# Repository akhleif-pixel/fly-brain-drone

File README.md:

# Fly-Brain Drone

A small ESP32-S3 camera quadcopter steered by a simulated fruit fly brain (FlyWire connectome, Shiu et al. 2024 model) running on a laptop.

- **Plan, phases and tasks:** https://claude.ai/artifact/NuM1vron4UPJLkWDwymUnH
- **Parts with photos and links:** https://claude.ai/artifact/14MLLZMBsPiJeyRGL1XqSZ
- **Project context for Claude:** [CLAUDE.md](CLAUDE.md)

## Folders

| Folder | What goes there | Owner |
| --- | --- | --- |
| `brain/` | Brain model setup and the laptop control loop | Person A |
| `drone/` | ESP32-S3 firmware (PlatformIO) | Person B |
| `frame/` | 3D-print files | Person B |
| `docs/` | Parts, wiring, notes | Both |

## Working together

**Ayham** works with Claude. **Ahmed** works in KiCad 10 on the PCB frame.

Ahmed, to get the files:
1. Accept the GitHub invite (email or github.com/notifications).
2. Install [GitHub Desktop](https://desktop.github.com), sign in, choose **File → Clone repository**, and pick `akhleif-pixel/fly-brain-drone`.
3. Open `pcb/kicad/fly-drone.kicad_pro` in KiCad. Start with [pcb/README.md](pcb/README.md).
4. When you've changed something: in GitHub Desktop, write a short summary, click **Commit**, then **Push origin**. Click **Fetch / Pull** before you start work to get Ayham's changes.

Both of you: pull before you start, and push when you're done. Don't edit the same file at the same time; Git will flag a conflict if you do.

When a decision changes, update `CLAUDE.md` so Claude knows.

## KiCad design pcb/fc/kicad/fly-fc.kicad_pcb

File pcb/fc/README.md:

# Flight-controller board, rev B

A small 46 × 44 mm, 2-layer board, about 4.7 g at 1.0 mm thick. It replaces the X-shaped PCB frame (rev A, in `pcb/`): the motors now sit in a 3D-printed frame and their wires come in to pads at this board's corners. Every part is through-hole, so it can be hand-soldered.

The silkscreen has **no text** on purpose: Ayham is adding his own labels in KiCad. Only part outlines, diode stripes, MOSFET tab bars and a front arrow are printed. (To bring back the generator's labels, set `TEXT = True` in `gen.py`.)

- **Top (parts side):** MOSFETs standing along the left and right edges, diodes and resistors beside them, the MPU6050 in the middle. Ground pour.
- **Bottom:** battery-plus (VBAT) pour, plus the gate traces.
- **TPS63020:** the real module (27.5 × 18.7 mm) is too big for the board, so it sits on foam under the ESP32, between its pin rows. VIN and GND come down to the rear IN and GND pads; OUT goes straight to the ESP32's 3V3 pin, which feeds this board through the front 3V3 pad.
- **ESP32:** held above the board by the printed frame, at least 13 mm up so it clears C1 and the MPU6050. The MOSFETs (about 18 mm tall) stand outside its footprint.

Regenerate everything with `pcb/.venv/Scripts/python pcb/fc/gen.py`, then check the netlist with `pcb/.venv/Scripts/python pcb/fc/_net.py`. The last run passed all checks: the generator's clearance, edge, drill and connectivity report; the netlist and MOSFET pin order; and KiCad 10.0.6 DRC (0 errors, 0 unconnected, only "footprint library not found" warnings).

The KiCad project is `kicad/fly-fc.kicad_pro`. Once someone saves the board in KiCad, that file is the master copy and `gen.py` won't overwrite it.

## Ordering

Upload `out/fly-fc-gerbers.zip`. Same settings as rev A: 2 layers, 1.0 mm, HASL lead-free, 1 oz copper, 5 pcs. The factory viewer should show a rounded square, 60 plated holes and 4 unplated corner holes.

## Pads

| Pad | Goes to | What it is |
| --- | --- | --- |
| M1+ / M1− … M4+ / M4− (corners) | Motor wires | + is battery plus, − is switched by the MOSFET |
| G1, G2, G3, G4 (front) | ESP32 GPIO 21, 47, 14, 38 | Motor 1–4 gates |
| SCL, SDA, INT (front) | ESP32 GPIO 42, 41, 40 | MPU6050 |
| 3V3, GND (front) | ESP32 3V3, GND | 3.3 V supply to the ESP32 |
| BAT + / − (rear) | Battery pigtail | |
| GND, IN (rear) | TPS63020 GND, VIN | Its OUT goes to the ESP32 3V3 pin, not to the board |

Motors: M1 front-right CCW, M2 rear-right CW, M3 rear-left CCW, M4 front-left CW.

Front pads, left to right: G4, G3, 3V3, SCL, SDA, GND, INT, G2, G1. Rear pads, left to right: BAT+ (square), BAT−, GND, IN, C1− and C1+ (square).

## Assembly order

1. Resistors R1–R4, lying flat.
2. Diodes D1–D4, lying flat, stripe on the square pad (the end nearer the middle of the board).
3. MOSFETs Q1–Q4 standing upright, **metal tab toward the board edge** (the white bar on the outline). The printed face looks at the middle of the board.
4. C1 standing, + on the square pad.
5. MPU6050 on its header, chips up, body toward the rear (over the board, not hanging off the front).
6. Battery pigtail into BAT + (square) and −.
7. TPS63020 on the bench: bridge its 3V3 pad and EN to VIN, solder short VIN, GND and OUT wires, connect the battery and **measure 3.3 V at OUT before going on.** Then stick it with foam tape to the underside of the ESP32, between the pin rows, VIN end toward the USB ports.
8. Screw the board into the frame, then solder the motor wires into the corner pads.
9. Short wires from the front pads up to the ESP32's pins. The TPS63020's VIN and GND wires go to the rear IN and GND pads; its OUT goes into the ESP32's 3V3 pin next to the wire from the front 3V3 pad.
10. Props off: check the spin directions. If a motor spins the wrong way, swap its two wires.

## Checked against the real parts (photos with a ruler, 2026-10-26)

- **IRLB8721:** genuine IR part, about 10.5 × 16.6 mm. The MOSFET holes are 1.2 mm so any TO-220 leg fits.
- **GY-521:** pins VCC GND SCL SDA XDA XCL AD0 INT, matching the board. Its header is already soldered on.
- **ESP32-S3 WROOM CAM board:** about 28.5 × 51 mm plus a 7 mm antenna overhang, two rows of 20 pins 25.4 mm apart. Its printed labels include every pin in our plan (GPIO 21, 47, 14, 38, 42, 41, 40, 3V3, GND).
- **8520 motors:** about 8.3 mm across, 20 mm long; CW motors have red/blue leads, CCW white/black.
- **TPS63020 module: about 27.5 × 18.7 mm**, too big for the board, so it moved under the ESP32 (the frame generator checks it clears the MPU6050 by 3.7 mm and C1 by 1.8 mm). Its pins: GND and VIN at one end, GND and OUT at the other, EN and PS on one long edge, and solder pads to pick 3.3 V, 4.2 V or 5 V. **Bridge the 3V3 pad and measure the output before connecting anything.**

The printed frame is in [frame/](../../frame/README.md).

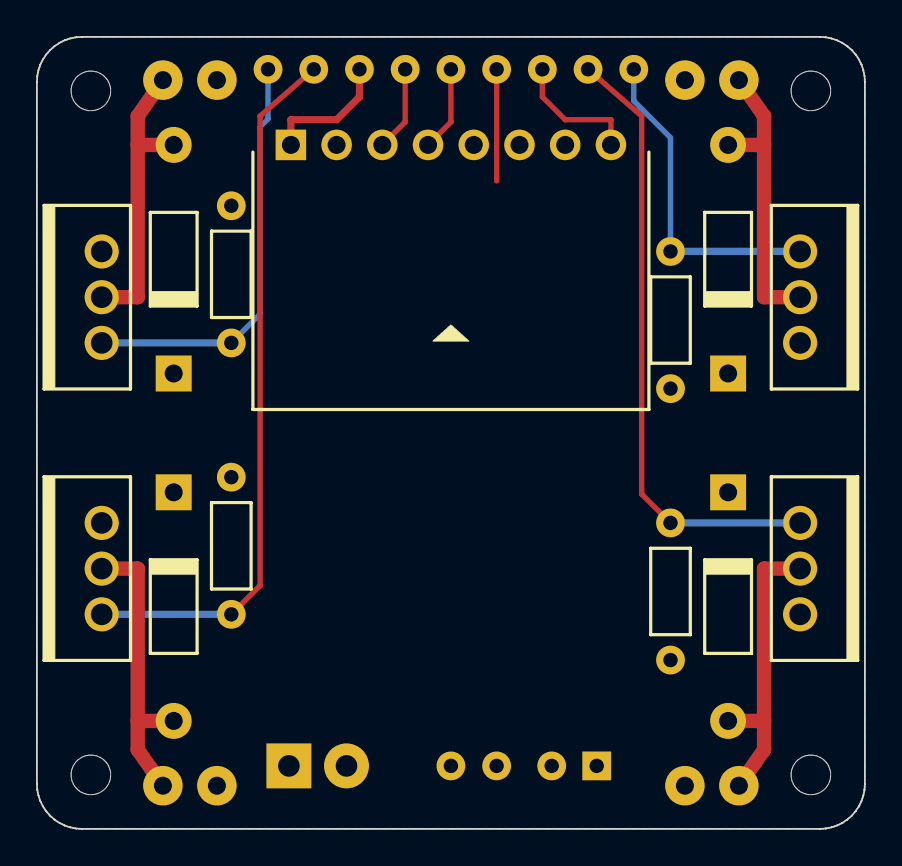
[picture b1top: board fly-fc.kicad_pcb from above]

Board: 2 copper layers, 46.0 x 44.0 mm, 34 parts (0 on the bottom side), 14 nets.

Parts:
BAT: battery pigtail; BAT
C1: 100uF; C1
D1: 1N5819; D1
D2: 1N5819; D2
D3: 1N5819; D3
D4: 1N5819; D4
H1, H2, H3, H4: M2; MountingHole_M2
J_3V3: wire pad; J_3V3
J_G1: wire pad; J_G1
J_G2: wire pad; J_G2
J_G3: wire pad; J_G3
J_G4: wire pad; J_G4
J_GND: wire pad; J_GND
J_IN: wire pad; J_IN
J_INT: wire pad; J_INT
J_SCL: wire pad; J_SCL
J_SDA: wire pad; J_SDA
J_TG: wire pad; J_TG
M1: 8520 motor; M1
M2: 8520 motor; M2
M3: 8520 motor; M3
M4: 8520 motor; M4
Q1: IRLB8721; Q1
Q2: IRLB8721; Q2
Q3: IRLB8721; Q3
Q4: IRLB8721; Q4
R1: 10k; R1
R2: 10k; R2
R3: 10k; R3
R4: 10k; R4
U2: GY-521 MPU6050; U2

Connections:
3V3: J_3V3.1, U2.VCC
DRAIN1: D1.A, M1.2, Q1.D
DRAIN2: D2.A, M2.2, Q2.D
DRAIN3: D3.A, M3.2, Q3.D
DRAIN4: D4.A, M4.2, Q4.D
GATE1: J_G1.1, Q1.G, R1.1
GATE2: J_G2.1, Q2.G, R2.1
GATE3: J_G3.1, Q3.G, R3.1
GATE4: J_G4.1, Q4.G, R4.1
GND: BAT.2, C1.2, J_GND.1, J_TG.1, Q1.S, Q2.S, Q3.S, Q4.S, R1.2, R2.2, R3.2, R4.2, U2.GND
INT: J_INT.1, U2.INT
SCL: J_SCL.1, U2.SCL
SDA: J_SDA.1, U2.SDA
VBAT: BAT.1, C1.1, D1.K, D2.K, D3.K, D4.K, J_IN.1, M1.1, M2.1, M3.1, M4.1

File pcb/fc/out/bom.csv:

Ref,Part,Qty
Q1-Q4,"IRLB8721 N-MOSFET, TO-220, standing upright, metal tab facing the board edge",4
D1-D4,"1N5819 Schottky, DO-41, lying flat, stripe on the square pad (toward the center line)",4
R1-R4,"10 kOhm 1/4 W, lying flat, 7.62 mm pitch",4
C1,"100 uF 16-25 V electrolytic, standing, + on the square pad",1
U2,"GY-521 MPU6050 on its 8-pin header, chips up, body toward the rear",1
TPS,"TPS63020 3.3 V buck-boost (27.5 x 18.7 mm) on foam under the ESP32: VIN and GND to the rear IN and GND pads, OUT to the ESP32 3V3 pin, EN bridged to VIN, 3V3 pad bridged",1
ESP32,"ESP32-S3 CAM board held above by the printed frame, wired from the front pads",1
M1-M4,"8520 motors in the printed frame, wires to the corner pads",4
BAT,1S 500 mAh battery pigtail into BAT+ and BAT-,1
Screws,4x M2 through the corner holes into the frame,4
